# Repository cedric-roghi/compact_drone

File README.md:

# compact_drone
compact contra rotating drone

Progress Update (15/10/26):
- Tolerances have been tightened. Best method so far is to print everything very tight and to sand down parts with 1000 grit.
- Used Mistral AI to review my code and suggest adding a phase offset to the rotor controls. I had been focusing too much on drone control systems that I had overlooked critical physical effects of helicopter mechanical control systems. A phase offset of -25 degrees seems to remove most toilet bowl effect I was seeing.

https://github.com/user-attachments/assets/04978339-0f8a-490a-9869-5cce7a8ede1a

Progress Update (17/09/26):
- I have been making further tuning and tweaking to the PID gains.
- Built a simple landing gear system out of wood and a 3D printed adapter to screw onto the drone frame.
- I have got some first flight attempts with the drone hopping around the garden in a semi-controlled way.

https://github.com/user-attachments/assets/63424fa8-df9c-4474-a59d-4073fd4611da

Progress Update (09/09/26):
- The yaw controls are working. I have found some PID gains that seem stable at low and high rotor speeds. I am planning on making a PyQT application to adjust flight controller settings without flashing the microcontroller.
- I used hot glue to fix the servo motors more securely and printed some new link rods to reduce play in the swash-plate.
- The swash-plate currently has too much play where the drone cannot correct error when its too small and leads to uncontrollable oscillation.

https://github.com/user-attachments/assets/415317f5-2f4a-4eaa-9d52-048ebe863607

## Table of Contents
- [Requirements](#requirements)
- [Rationale](#rationale)
- [Installation](#installation)
- [Usage](#usage)
- [Features](#features)
- [Future_Additions](#future_additions)
- [Configuration](#configuration)
- [Known_Issues](#known_issues)

## Requirements
- Software:
    - Freecad (for 3D part design)
    - KICAD (PCB design)
    - ST Cube IDE (ST account required for download)
- Hardware:
    - BOM to come
    - Access to a 3D printer

## Rationale
I did not come up with the design idea of a tube shaped coaxial drone. Despite it being a rare design I got inspiration from projects such as [backcountrydrones](https://www.youtube.com/watch?v=82phDhYGT_0) and [Tdrone](https://github.com/ShenZhenAccelerationTechCo/Tdrone). BackcountryDrones guys have now changed to Ascent Aerosystems and make military/law enforcement and industrial coaxial drones. The NASA mars copter is another example of a contra rotating drone design.

The idea is that the propellers can fold down which means the drone can fit in smaller storage solutions. Not only does the the tube shape enable a smaller size when storing the drone but it also helps make it more rugged and resistant to poor treatment. A final goal for this project would be to have a drone I can strap to the outside of a hiking pack without having to worry about damage. 

Using a coaxial design is more efficient in theory. Having two large propeller spinning about the center of the drone increases the lifting disc area compared to having four propellers next to each other that will waste space. A coaxial drone with a tube shape also reduces its surface area when tilting forwards to move making it more streamlined than a quadcopter that shows more surface area to drag when moving forward. I recommend reading this paper from Ascent Aerosystems about all the advantages and its got diagrams (https://ascentaerosystems.com/wp-content/uploads/2024/12/Coaxial-Advantage-White-Paper-Ascent-AeroSystems.pdf).

Just because two propellers are stacked on top of each other does not actually mean I get double the lift of normal helicopter. Based on a small amount of research I have done, it would seem that while coaxial drones can be more efficient and reduce turbulent airflow they do not multiply thrust by two. Basically the thrust gain is not linear. Source (https://www.ligpower.com/blog/conventional-vs-coaxial-drone-motors.html).

Figures from the Ascent Aerosystems paper (https://ascentaerosystems.com/wp-content/uploads/2024/12/Coaxial-Advantage-White-Paper-Ascent-AeroSystems.pdf).

Some applications for the drone would be for survey work in remote areas, filming, compact and rapid deployment via stackable launch cells. In theory it could even be launched from a plane like the Atlantique 2 which already has tube shaped launchers on the belly for sonars. The mass plane launch system could enable for massive detailed search areas using drone swarms for any use case that would require a search area like pest control, mountain rescue, security perimeters.

Atlantique 2 sonar buoys launcher.

- STM32f411:
    - Same MCU I used for my turret project. Its fast, powerful, and has many timers for pwm output. Since I used it for a previous turret project it makes the PCB development for the drone much faster.
    - Another great advantage of this MCU is that it can do up to 100MHz clock speed which gives me plenty of headroom for "high speed"(relative term) communications like UART or I2C, without preempting my critical FreeRTOS tasks.

Below are some pictures of the PCB and 3D design to be printed.

## Installation
program command for usb in BOOT 0 mode

dfu-util -a 0 -s 0x08000000:leave -D build/debug/Drone_Code.bin

or use an stlinkv2.

## Usage

## Features
- Flight Controller
    -  ICM42605 IMU
    -  MMC5603NJ Magnetometer
    -  BMP280 Barometer
    -  2 USART connections for ELRS receiver and a future upgrade
    -  SWD connector for debugging/flashing
    -  Green and Red status LEDs
    -  BOOT0 switch (to switch bootloader mode)
    -  Reset button
    -  Extra servo PWM connector for camera pitch control (idea is that there is no need for yaw since the drone spins around easily)
 
- Mechanical
    - Foldable propellers
    - Fully 3D printed body
    - 
## Future_Additions

## Configuration

## Known_Issues

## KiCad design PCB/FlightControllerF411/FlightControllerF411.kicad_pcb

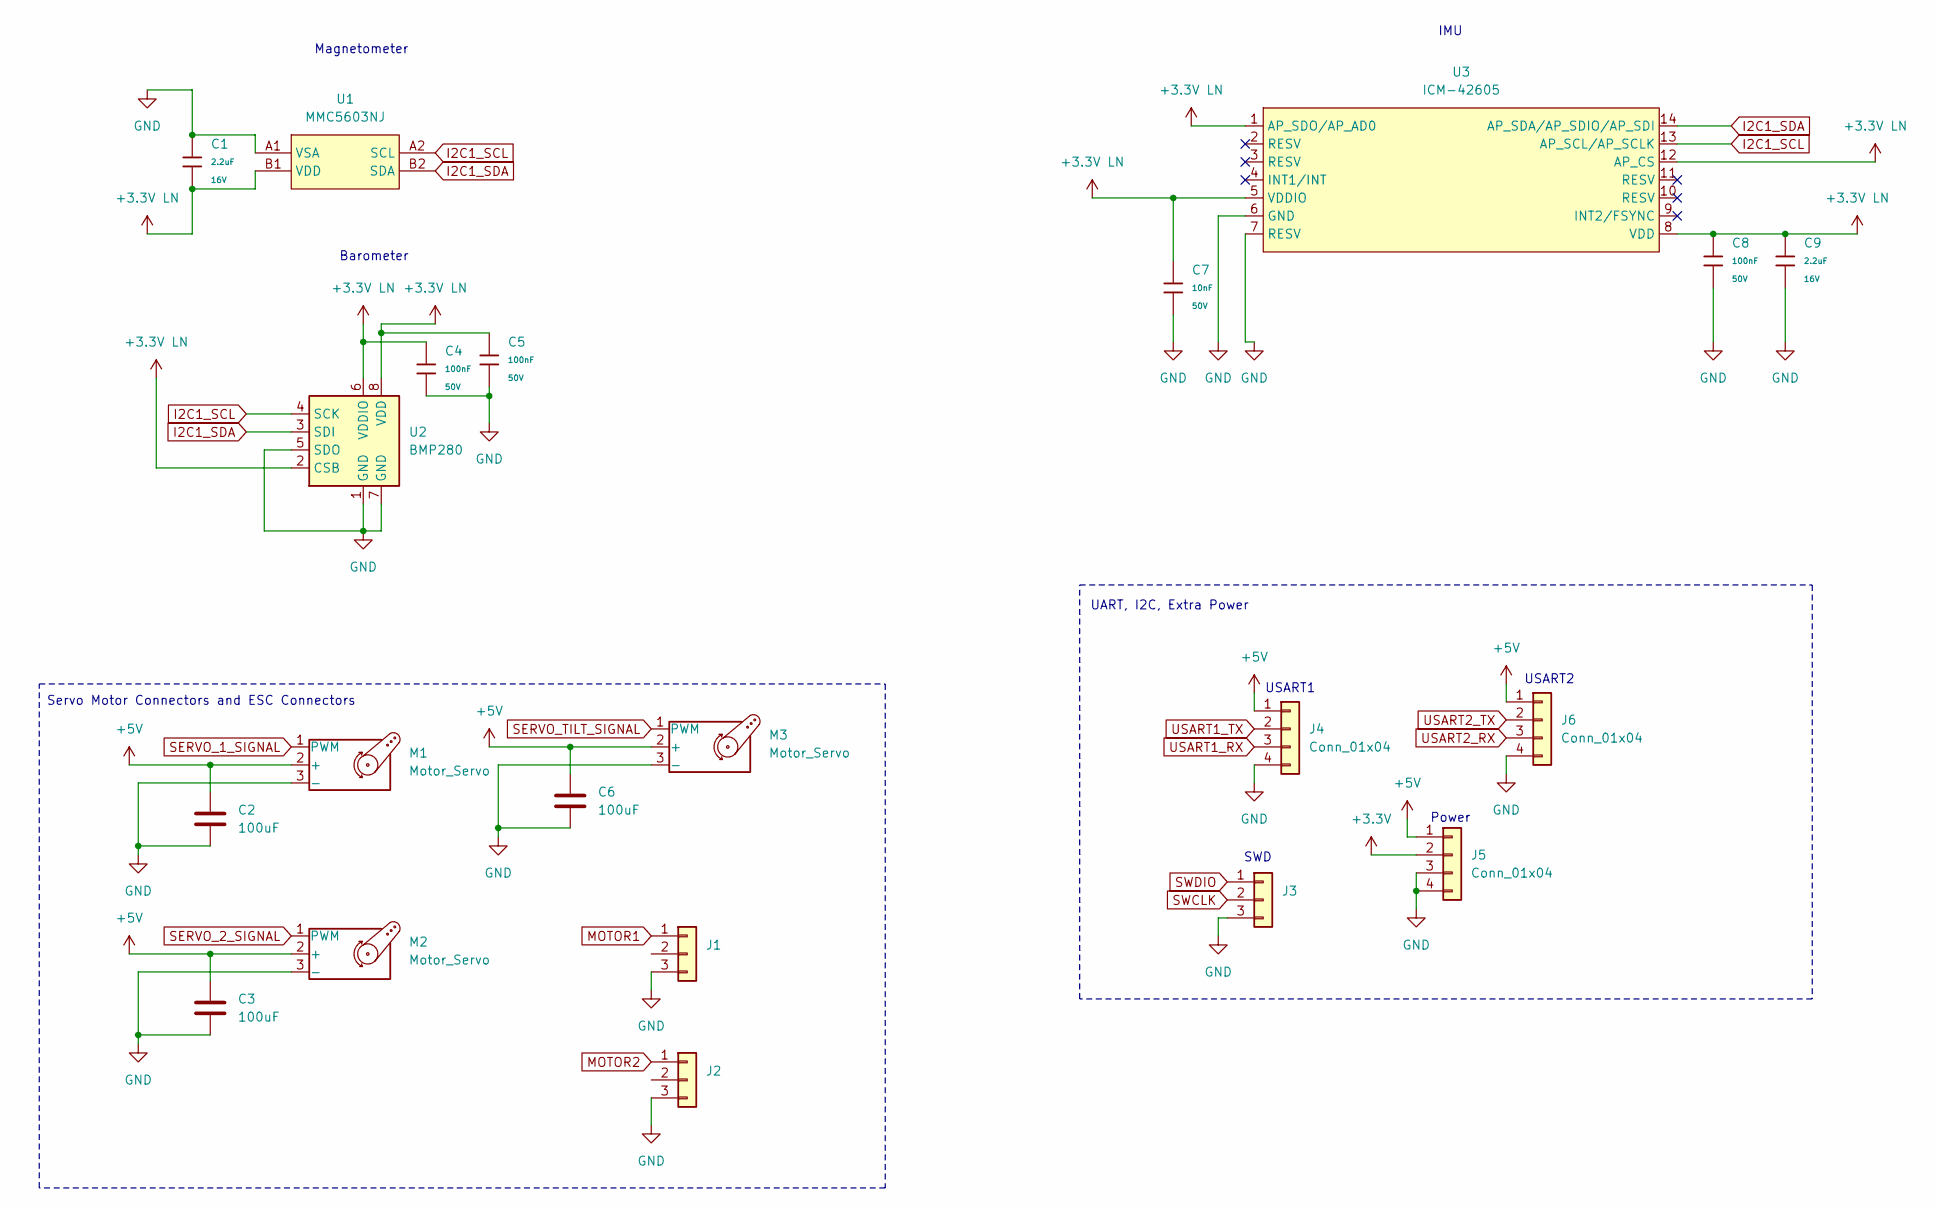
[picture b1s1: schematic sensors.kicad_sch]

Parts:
C1, C9: 2.2uF; C_0603; Voltage Rated 16V; Tolerance ±10%; Part CL10A225KO8NNNC; LCSC C23630
C2, C3, C6: 100uF; C_Radial_D6.3mm_H5.0mm_P2.50mm
C4, C5, C8: 100nF; C_0603; Voltage Rated 50V; Tolerance ±10%; Part CC0603KRX7R9BB104; LCSC C14663
C7: 10nF; C_0603; Voltage Rated 50V; Tolerance ±10%; Part 0603B103K500NT; LCSC C57112
J1, J2, J3: Conn_01x03; PinHeader_1x03_P2.54mm_Vertical
J4, J5, J6: Conn_01x04; PinHeader_1x04_P2.54mm_Vertical
M1, M2, M3: Motor_Servo; PinHeader_1x03_P2.54mm_Vertical
U1: MMC5603NJ; FLIPCHIP-4_L0.8-W0.8-R2-C2-P0.40-TL; MPN MMC5603NJ; LCSC Part C404328
U2: BMP280; Bosch_LGA-8_2x2.5mm_P0.65mm_ClockwisePinNumbering
U3: ICM-42605; LGA-14_L3.0-W2.5-P0.50-TL; MPN ICM-42605; LCSC Part C2655099

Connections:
+3.3V: J5.2; also elsewhere on the board
+3.3V LN: C1.2, C4.1, C5.1, C7.1, C8.1, C9.1, U1.B1 (VDD), U2.2 (CSB), U2.6 (VDDIO), U2.8 (VDD), U3.1 (AP_SDO/AP_AD0), U3.5 (VDDIO), U3.8 (VDD), U3.12 (AP_CS); also elsewhere on the board
+5V: C2.1, C3.1, C6.1, J4.1, J5.1, J6.1, M1.2 (+), M2.2 (+), M3.2 (+); also elsewhere on the board
GND: C1.1, C2.2, C3.2, C4.2, C5.2, C6.2, C7.2, C8.2, C9.2, J1.3, J2.3, J3.3, J4.4, J5.3, J5.4, J6.4, M1.3 (-), M2.3 (-), M3.3 (-), U1.A1 (VSA), U2.1 (GND), U2.5 (SDO), U2.7 (GND), U3.6 (GND), U3.7 (RESV); also elsewhere on the board
I2C1_SCL: U1.A2 (SCL), U2.4 (SCK), U3.13 (AP_SCL/AP_SCLK); also elsewhere on the board
I2C1_SDA: U1.B2 (SDA), U2.3 (SDI), U3.14 (AP_SDA/AP_SDIO/AP_SDI); also elsewhere on the board
MOTOR1: J1.1; also elsewhere on the board
MOTOR2: J2.1; also elsewhere on the board
SERVO_1_SIGNAL: M1.1 (PWM); also elsewhere on the board
SERVO_2_SIGNAL: M2.1 (PWM); also elsewhere on the board
SERVO_TILT_SIGNAL: M3.1 (PWM); also elsewhere on the board
SWCLK: J3.2; also elsewhere on the board
SWDIO: J3.1; also elsewhere on the board
USART1_RX: J4.3; also elsewhere on the board
USART1_TX: J4.2; also elsewhere on the board
USART2_RX: J6.3; also elsewhere on the board
USART2_TX: J6.2; also elsewhere on the board

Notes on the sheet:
USART1
Servo Motor Connectors and ESC Connectors
UART, I2C, Extra Power
Power
SWD
Magnetometer
Barometer
IMU
USART2

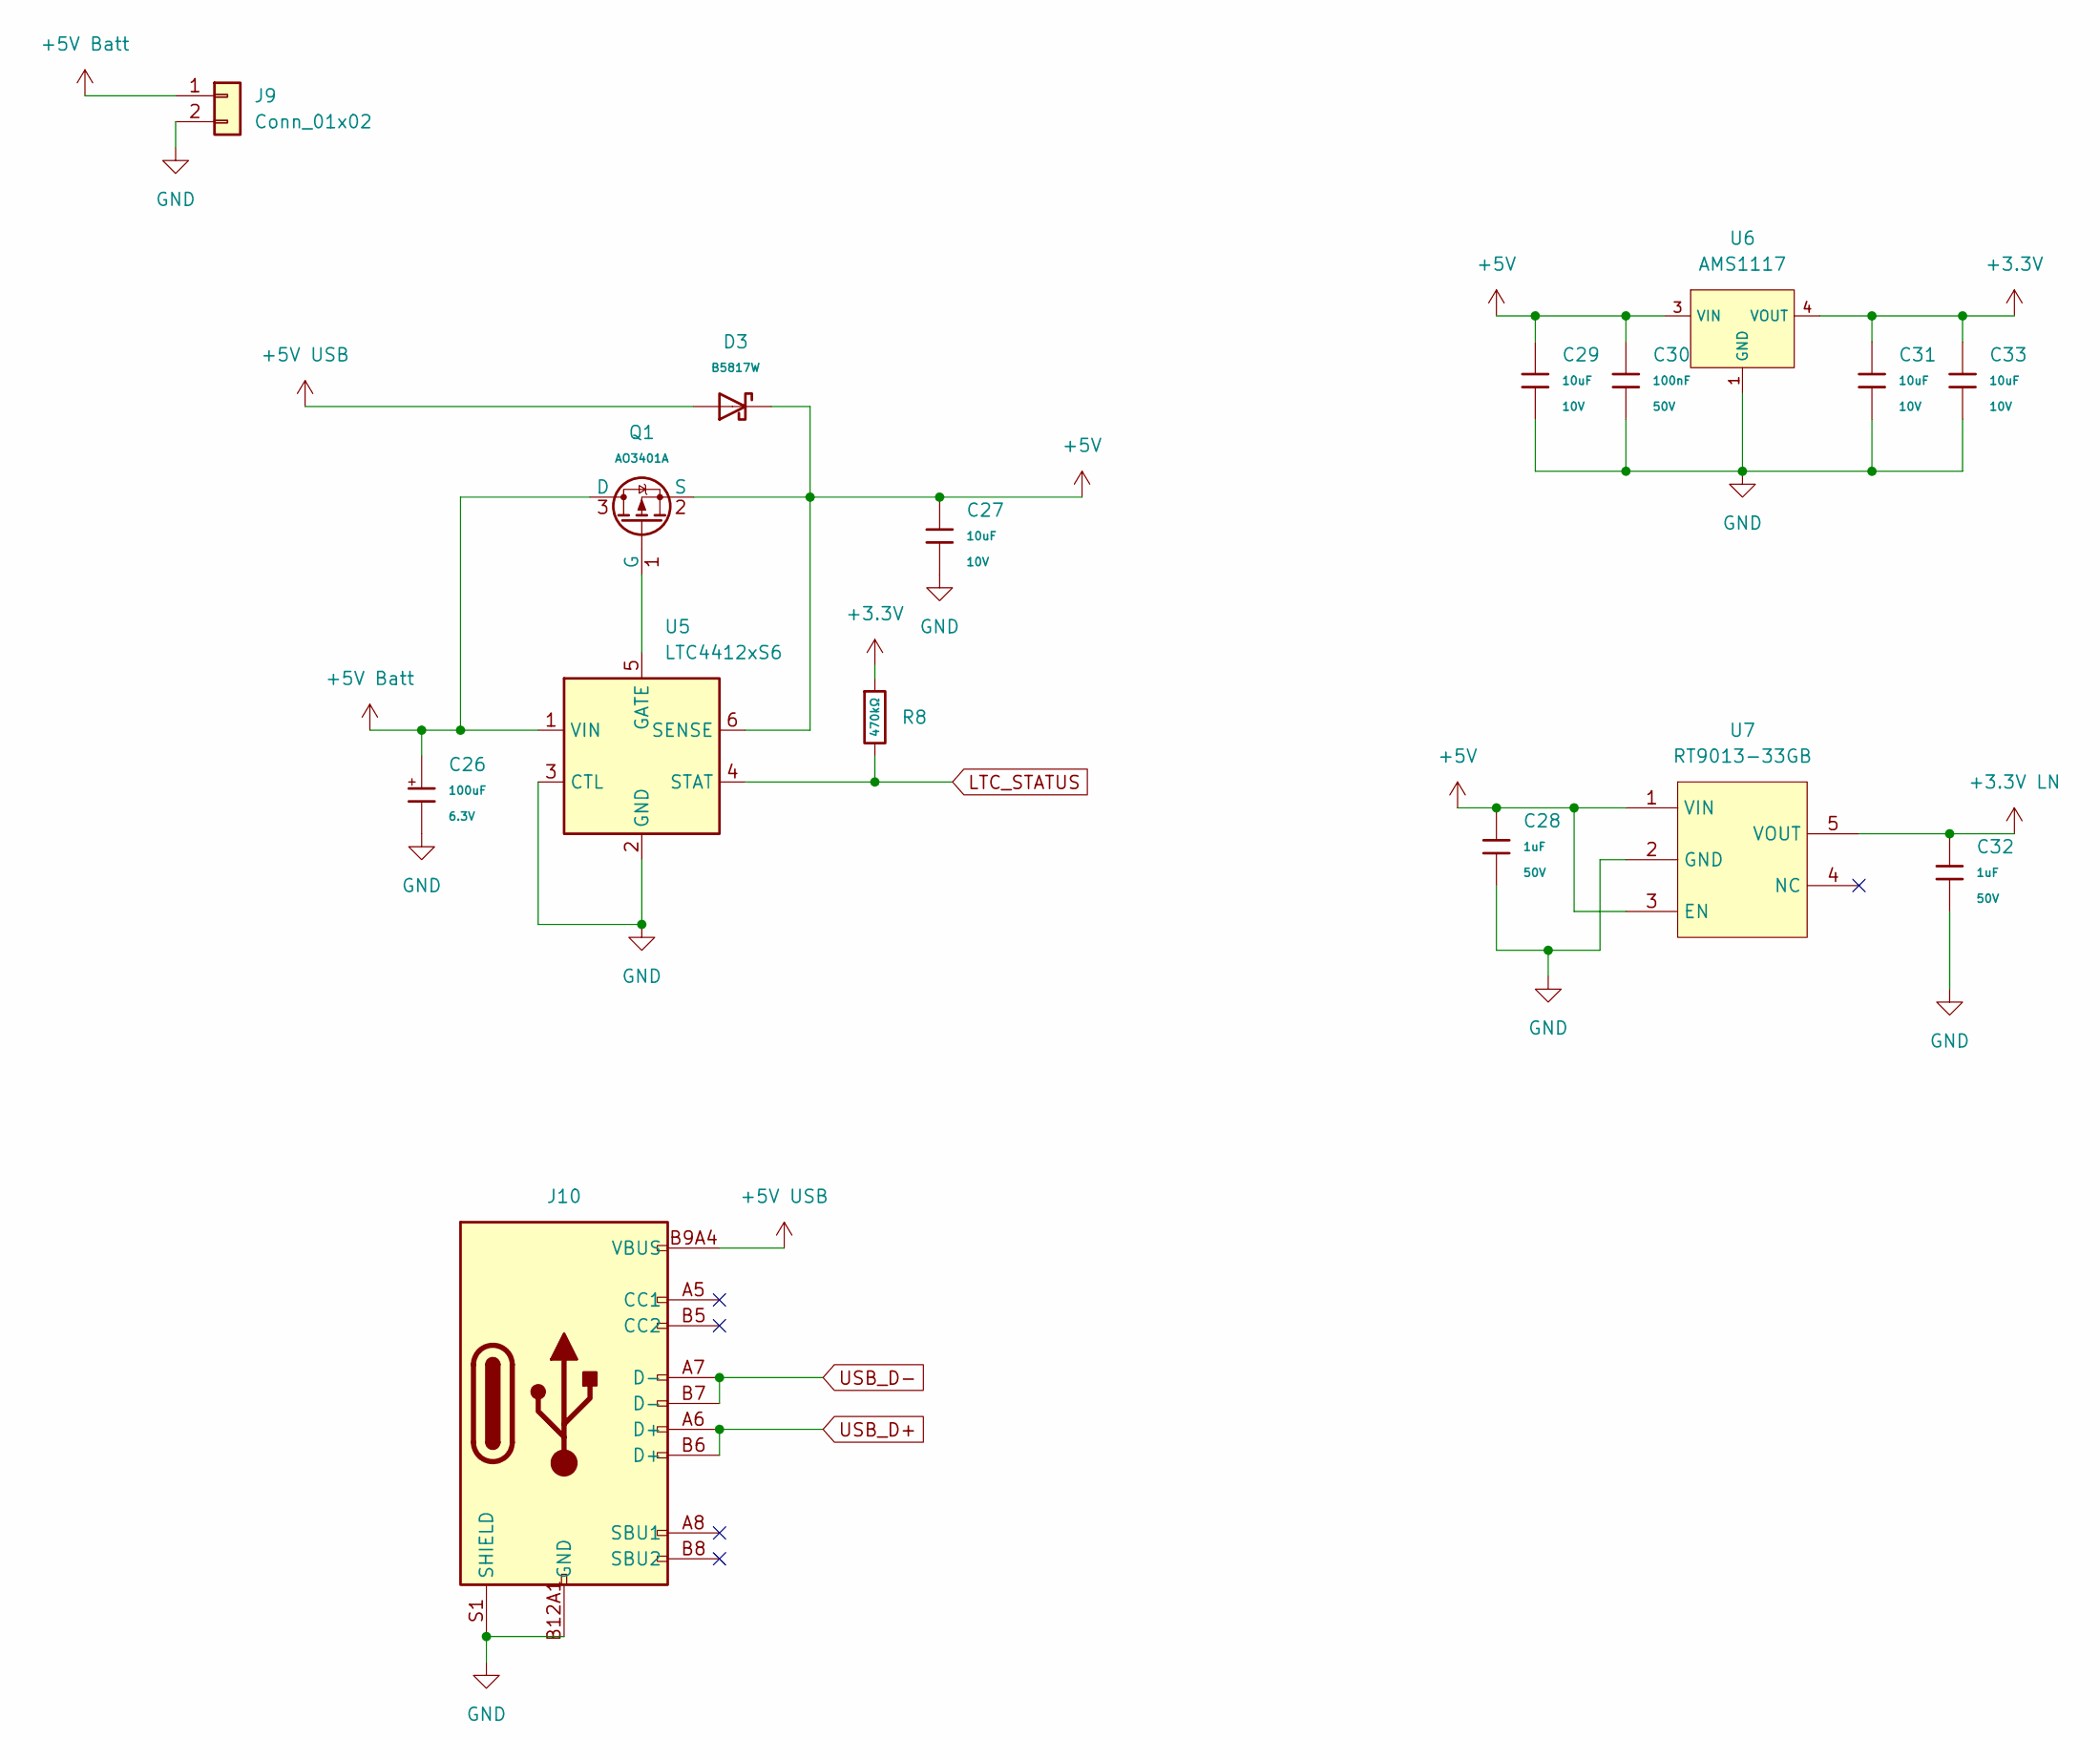
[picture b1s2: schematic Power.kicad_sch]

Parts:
C26: 100uF; C_CASE-B-3528-21(mm); Tolerance ±10%; Rated Voltage 6.3V; Part TAJB107K006RNJ; LCSC C16133
C27, C29, C31, C33: 10uF; C_0603; Voltage Rated 10V; Tolerance ±10%; Part CL10A106KP8NNNC; LCSC C19702
C28, C32: 1uF; C_0603; Voltage Rated 50V; Tolerance ±10%; Part CL10A105KB8NNNC; LCSC C15849
C30: 100nF; C_0603; Voltage Rated 50V; Tolerance ±10%; Part CC0603KRX7R9BB104; LCSC C14663
D3: B5817W; D_SOD-123; Forward Voltage (Vf@If) 0.45V@1.0A; Reverse Voltage (Vr) 20V; Part B5817W; LCSC C7420328
J9: Conn_01x02; PinHeader_1x02_P2.54mm_Vertical
J10: Connector, USB-TYPE-C-16P; TYPE-C-SMD_HX-TYPE-C-16PIN; LCSC C2927039
Q1: AO3401A; Q_SOT-23; Part AO3401A; LCSC C15127
R8: 470kΩ; R_0603; Overload Voltage (Max) 75V; Tolerance ±1%; Part 0603WAF4703T5E; LCSC C23178
U5: LTC4412xS6; TSOT-23-6
U6: AMS1117; SOT-223-3_L6.5-W3.4-P2.30-LS7.0-BR; Output Voltage 3.3V; Dropout Voltage 1.3V@(800mA); Part AMS1117-3.3; LCSC C6186
U7: RT9013-33GB; SOT-23-5_L3.0-W1.7-P0.95-LS2.8-BL; MPN RT9013-33GB; LCSC Part C47773

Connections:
+3.3V: C31.1, C33.1, R8.1, U6.2 (VOUT), U6.4 (VOUT); also elsewhere on the board
+3.3V LN: C32.1, U7.5 (VOUT); also elsewhere on the board
+5V: C27.1, C28.1, C29.1, C30.1, D3.1, Q1.2 (S), U5.6 (SENSE), U6.3 (VIN), U7.1 (VIN), U7.3 (EN); also elsewhere on the board
+5V Batt: C26.1, J9.1, Q1.3 (D), U5.1 (VIN)
+5V USB: D3.2, J10.A9B4 (VBUS), J10.B9A4 (VBUS)
GND: C26.2, C27.2, C28.2, C29.2, C30.2, C31.2, C32.2, C33.2, J9.2, J10.A12B1 (GND), J10.B12A1 (GND), J10.S1 (SHIELD), U5.2 (GND), U5.3 (CTL), U6.1 (GND), U7.2 (GND); also elsewhere on the board
LTC_STATUS: R8.2, U5.4 (STAT)
unnamed: Q1.1 (G), U5.5 (GATE)
USB_D+: J10.A6 (D+), J10.B6 (D+); also elsewhere on the board
USB_D-: J10.A7 (D-), J10.B7 (D-); also elsewhere on the board

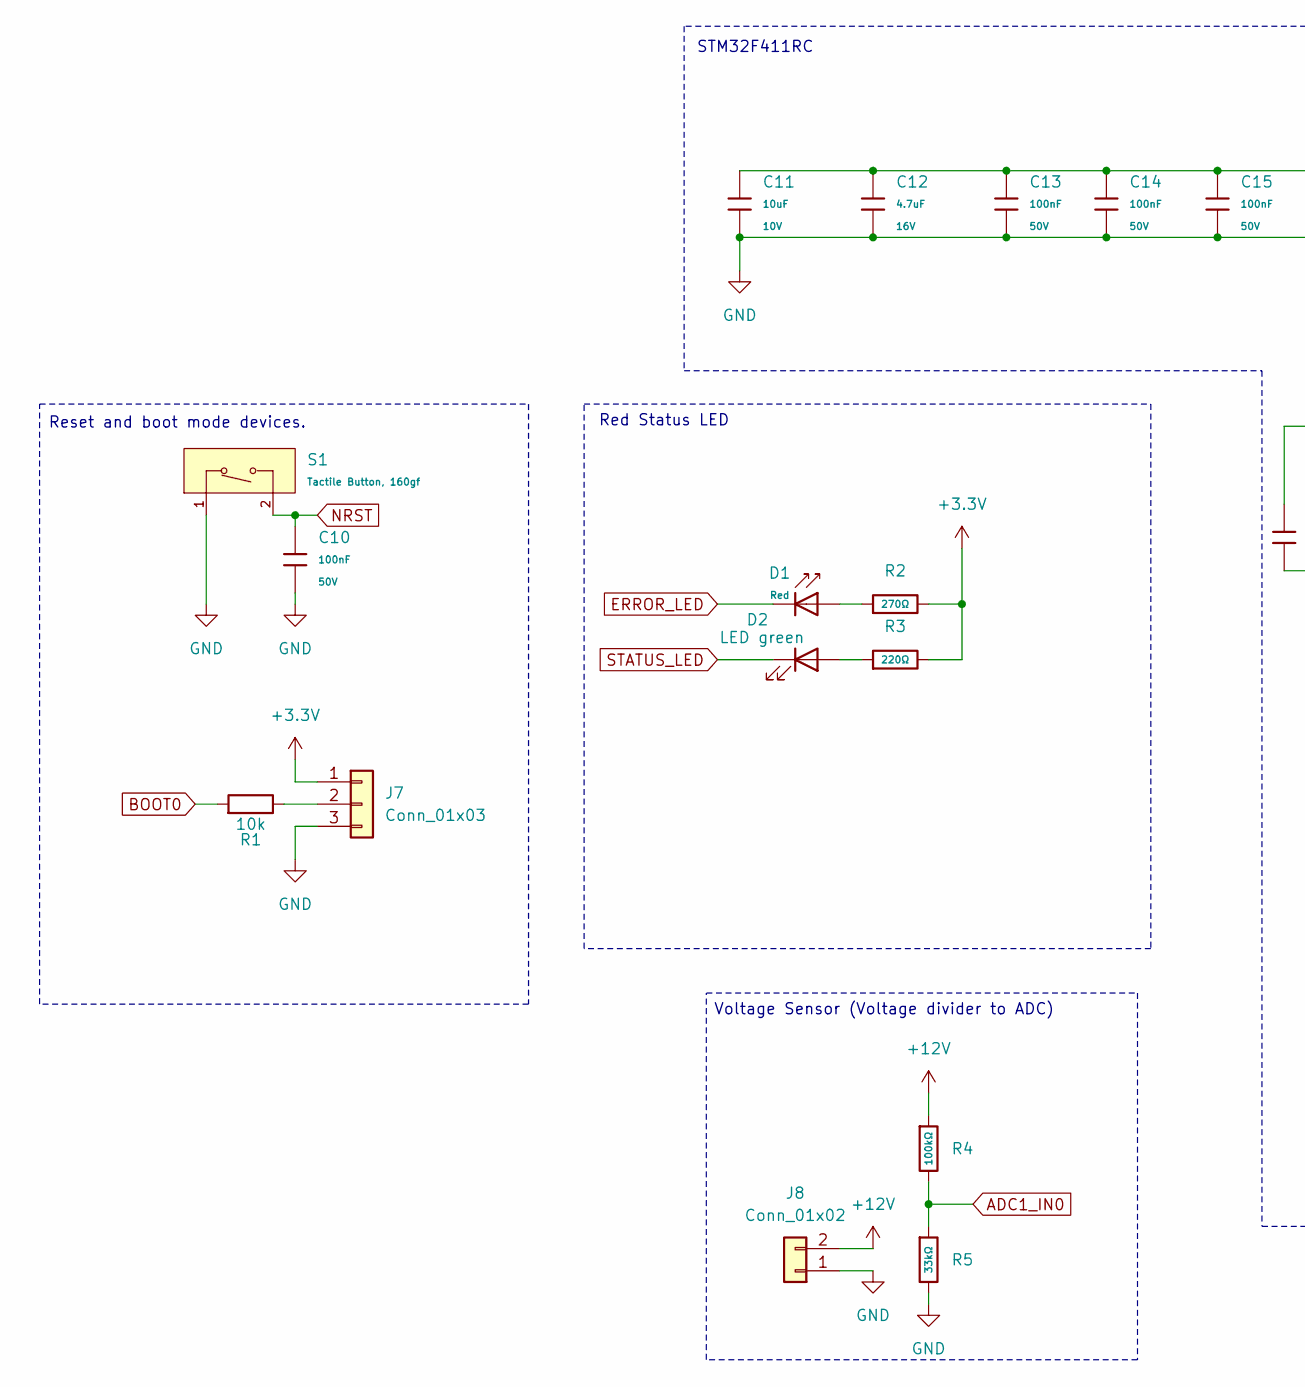
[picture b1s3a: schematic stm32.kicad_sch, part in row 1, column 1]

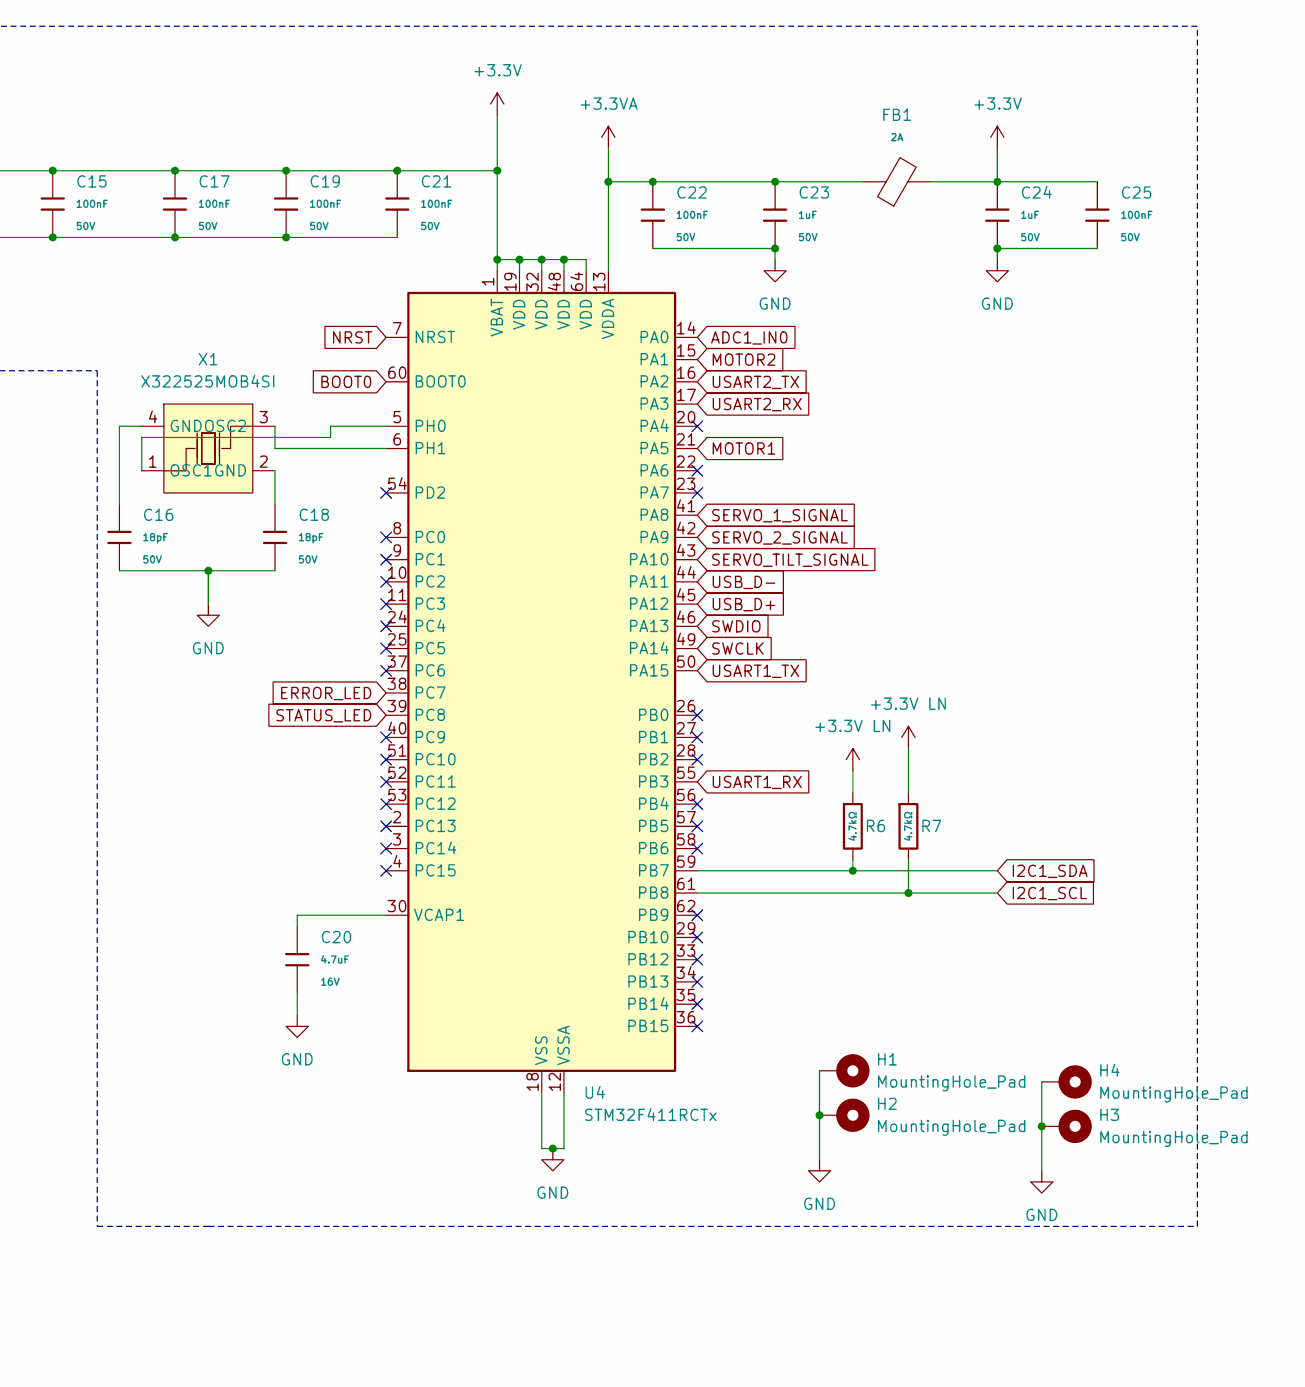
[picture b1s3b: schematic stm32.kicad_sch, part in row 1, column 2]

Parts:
C10, C13, C14, C15, C17, C19, C21, C22, C25: 100nF; C_0603; Voltage Rated 50V; Tolerance ±10%; Part CC0603KRX7R9BB104; LCSC C14663
C11: 10uF; C_0603; Voltage Rated 10V; Tolerance ±10%; Part CL10A106KP8NNNC; LCSC C19702
C12, C20: 4.7uF; C_0603; Voltage Rated 16V; Tolerance ±10%; Part CL10A475KO8NNNC; LCSC C19666
C16, C18: 18pF; C_0603; Voltage Rated 50V; Tolerance ±5%; Part CL10C180JB8NNNC; LCSC C1647
C23, C24: 1uF; C_0603; Voltage Rated 50V; Tolerance ±10%; Part CL10A105KB8NNNC; LCSC C15849
D1: Red; D_0603; Part KT-0603R; LCSC C2286
D2: LED green; LED_0603_1608Metric_Pad1.05x0.95mm_HandSolder
FB1: FB_0603; Current Rating 2A; Tolerance ±25%; Part BLM18PG121SN1D; LCSC C14709
H1, H2, H3, H4: MountingHole_Pad; MountingHole_2.7mm_M2.5_DIN965_Pad
J7: Conn_01x03; PinHeader_1x03_P2.54mm_Vertical
J8: Conn_01x02; PinHeader_1x02_P2.54mm_Vertical
R1: 10k; R_0603_1608Metric_Pad0.98x0.95mm_HandSolder
R2: 270Ω; R_0603; Overload Voltage (Max) 75V; Tolerance ±1%; Part 0603WAF2700T5E; LCSC C22966
R3: 220Ω; R_0603; Overload Voltage (Max) 75V; Tolerance ±1%; Part 0603WAF2200T5E; LCSC C22962
R4: 100kΩ; R_0603; Overload Voltage (Max) 75V; Tolerance ±1%; Part 0603WAF1003T5E; LCSC C25803
R5: 33kΩ; R_0603; Overload Voltage (Max) 75V; Tolerance ±1%; Part 0603WAF3302T5E; LCSC C4216
R6, R7: 4.7kΩ; R_0603; Overload Voltage (Max) 75V; Tolerance ±1%; Part 0603WAF4701T5E; LCSC C23162
S1: Tactile Button, 160gf; SW_TS-1088-AR02016; Voltage Rating (Dc) 12V; Part TS-1088-AR02016; LCSC C720477
U4: STM32F411RCTx; LQFP-64_10x10mm_P0.5mm
X1: X322525MOB4SI; CRYSTAL-SMD_4P-L3.2-W2.5-BL; MPN X322525MOB4SI; LCSC Part C9006

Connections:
+3.3V: C11.1, C12.1, C13.1, C14.1, C15.1, C17.1, C19.1, C21.1, C24.1, C25.1, FB1.2, J7.1, R2.2, R3.2, U4.1 (VBAT), U4.19 (VDD), U4.32 (VDD), U4.48 (VDD), U4.64 (VDD); also elsewhere on the board
+3.3V LN: R6.1, R7.1; also elsewhere on the board
+3.3VA: C22.1, C23.1, FB1.1, U4.13 (VDDA)
+12V: J8.2, R4.1
ADC1_IN0: R4.2, R5.1, U4.14 (PA0)
BOOT0: R1.2, U4.60 (BOOT0)
ERROR_LED: D1.1, U4.38 (PC7)
GND: C10.2, C11.2, C12.2, C13.2, C14.2, C15.2, C16.2, C17.2, C18.2, C19.2, C20.2, C21.2, C22.2, C23.2, C24.2, C25.2, H1.1 (1_1), H2.1 (1_1), H3.1 (1_1), H4.1 (1_1), J7.3, J8.1, R5.2, S1.1 (A), U4.12 (VSSA), U4.18 (VSS), U4.31 (VSS), U4.47 (VSS), U4.63 (VSS); also elsewhere on the board
I2C1_SCL: R7.2, U4.61 (PB8); also elsewhere on the board
I2C1_SDA: R6.2, U4.59 (PB7); also elsewhere on the board
MOTOR1: U4.21 (PA5); also elsewhere on the board
MOTOR2: U4.15 (PA1); also elsewhere on the board
NRST: C10.1, S1.2 (B), U4.7 (NRST)
unnamed: C16.1, X1.4 (GND)
unnamed: C18.1, X1.2 (GND)
unnamed: D1.2, R2.1
unnamed: D2.2 (A), R3.1
unnamed: J7.2, R1.1
unnamed: U4.5 (PH0), X1.1 (OSC1)
unnamed: U4.6 (PH1), X1.3 (OSC2)
unnamed: C20.1, U4.30 (VCAP1)
SERVO_1_SIGNAL: U4.41 (PA8); also elsewhere on the board
SERVO_2_SIGNAL: U4.42 (PA9); also elsewhere on the board
SERVO_TILT_SIGNAL: U4.43 (PA10); also elsewhere on the board
STATUS_LED: D2.1 (K), U4.39 (PC8)
SWCLK: U4.49 (PA14); also elsewhere on the board
SWDIO: U4.46 (PA13); also elsewhere on the board
USART1_RX: U4.55 (PB3); also elsewhere on the board
USART1_TX: U4.50 (PA15); also elsewhere on the board
USART2_RX: U4.17 (PA3); also elsewhere on the board
USART2_TX: U4.16 (PA2); also elsewhere on the board
USB_D+: U4.45 (PA12); also elsewhere on the board
USB_D-: U4.44 (PA11); also elsewhere on the board

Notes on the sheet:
Red Status LED
STM32F411RC
Voltage Sensor (Voltage divider to ADC)
Reset and boot mode devices.

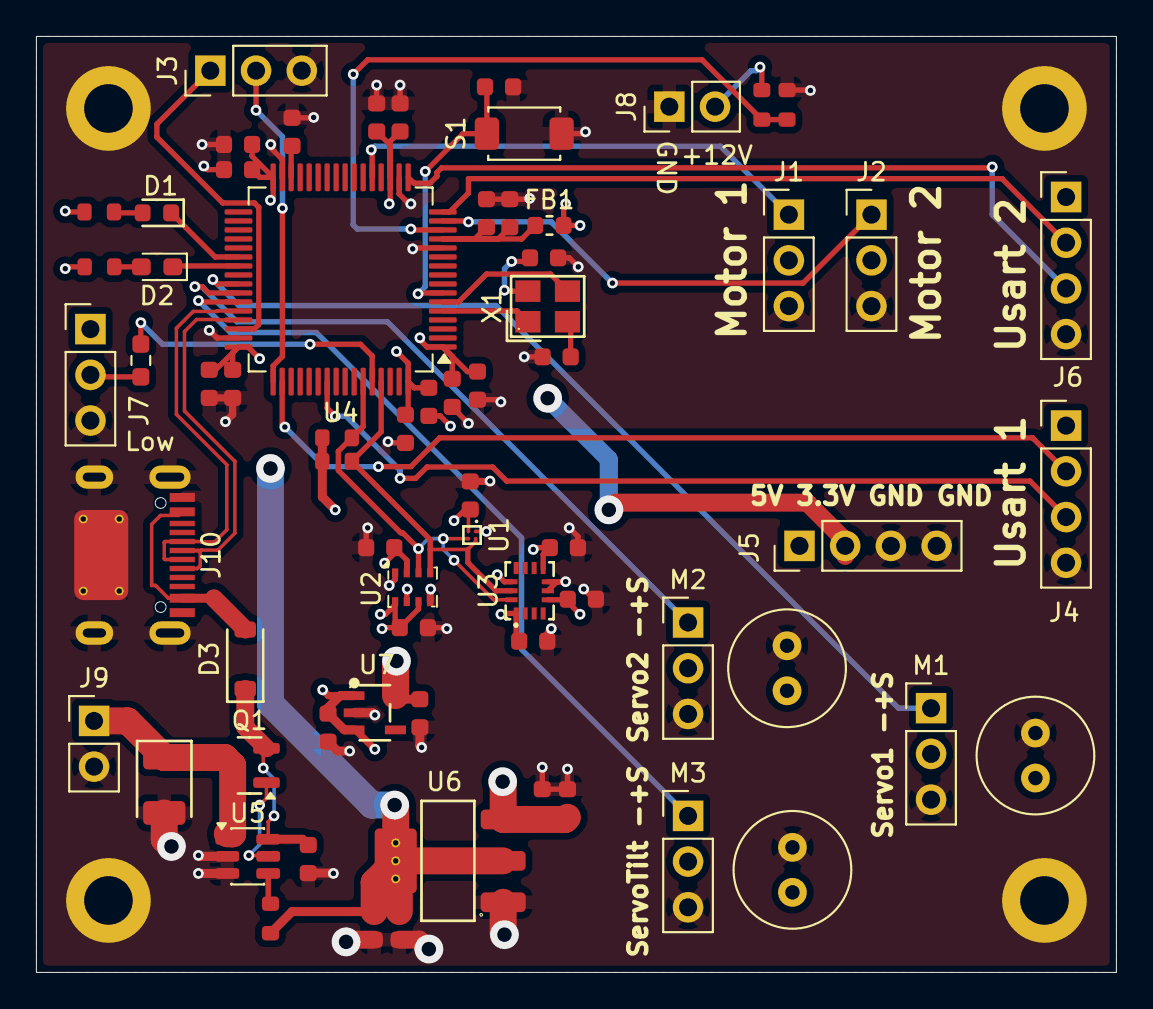
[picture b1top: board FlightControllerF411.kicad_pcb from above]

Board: 4 copper layers, 60.0 x 52.0 mm, 72 parts (0 on the bottom side), 38 nets.

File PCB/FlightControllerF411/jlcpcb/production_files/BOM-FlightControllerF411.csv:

Comment,Designator,Footprint,LCSC,Quantity
100kΩ,R4,R_0603,C25803,1
100nF,"C10,C13,C14,C15,C17,C19,C21,C22,C25,C30,C4,C5,C8",C_0603,C14663,13
100uF,C26,C_CASE-B-3528-21(mm),C16133,1
10k,R1,R_0603_1608Metric_Pad0.98x0.95mm_HandSolder,C25805,1
10nF,C7,C_0603,C57112,1
10uF,"C11,C27,C29,C31,C33",C_0603,C19702,5
18pF,"C16,C18",C_0603,C1647,2
1uF,"C23,C24,C28,C32",C_0603,C15849,4
2.2uF,"C1,C9",C_0603,C23630,2
220Ω,R3,R_0603,C22962,1
270Ω,R2,R_0603,C22966,1
33kΩ,R5,R_0603,C4216,1
4.7kΩ,"R6,R7",R_0603,C23162,2
4.7uF,"C12,C20",C_0603,C19666,2
470kΩ,R8,R_0603,C23178,1
AMS1117,U6,SOT-223-3_L6.5-W3.4-P2.30-LS7.0-BR,C6186,1
AO3401A,Q1,Q_SOT-23,C15127,1
B5817W,D3,D_SOD-123,C7420328,1
BMP280,U2,Bosch_LGA-8_2x2.5mm_P0.65mm_ClockwisePinNumbering,C83291,1
"Connector, USB-TYPE-C-16P",J10,TYPE-C-SMD_HX-TYPE-C-16PIN,C2927039,1
ICM-42605,U3,LGA-14_L3.0-W2.5-P0.50-TL,C2655099,1
LTC4412xS6,U5,TSOT-23-6,C514442,1
MMC5603NJ,U1,FLIPCHIP-4_L0.8-W0.8-R2-C2-P0.40-TL,C404328,1
RT9013-33GB,U7,SOT-23-5_L3.0-W1.7-P0.95-LS2.8-BL,C47773,1
STM32F411RCTx,U4,LQFP-64_10x10mm_P0.5mm,C222222,1
"Tactile Button, 160gf",S1,SW_TS-1088-AR02016,C720477,1
X322525MOB4SI,X1,CRYSTAL-SMD_4P-L3.2-W2.5-BL,C9006,1
~,FB1,FB_0603,C14709,1

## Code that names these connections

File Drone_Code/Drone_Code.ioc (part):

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Mcu.Name=STM32F411R(C-E)Tx
Mcu.Package=LQFP64
Mcu.UserName=STM32F411RCTx
PA0-WKUP.Signal=ADCx_IN0
PA1.GPIOParameters=GPIO_Label
PA1.GPIO_Label=Motor 2
PA1.Signal=S_TIM2_CH2
PA10.GPIOParameters=GPIO_Label
PA10.GPIO_Label=Servo Tilt
PA10.Signal=S_TIM1_CH3
PA11.Mode=Device_Only
PA11.Signal=USB_OTG_FS_DM
PA12.Mode=Device_Only
PA12.Signal=USB_OTG_FS_DP
PA13.Mode=Serial_Wire
PA13.Signal=SYS_JTMS-SWDIO
PA14.Mode=Serial_Wire
PA14.Signal=SYS_JTCK-SWCLK
PA15.Mode=Asynchronous
PA15.Signal=USART1_TX
PA2.Mode=Asynchronous
PA2.Signal=USART2_TX
PA3.Mode=Asynchronous
PA3.Signal=USART2_RX
PA5.GPIOParameters=GPIO_Label
PA5.GPIO_Label=Motor 1
PA5.Signal=S_TIM2_CH1_ETR
PA8.GPIOParameters=GPIO_Label
PA8.GPIO_Label=Servo 1
PA8.Signal=S_TIM1_CH1
PA9.GPIOParameters=GPIO_Label
PA9.GPIO_Label=Servo 2
PA9.Signal=S_TIM1_CH2
PB3.Mode=Asynchronous
PB3.Signal=USART1_RX
PB7.Mode=I2C
PB7.Signal=I2C1_SDA
PB8.Mode=I2C
PB8.Signal=I2C1_SCL
PC7.Signal=GPIO_Output
PC8.Signal=GPIO_Output
PH0\ -\ OSC_IN.Mode=HSE-External-Oscillator
PH0\ -\ OSC_IN.Signal=RCC_OSC_IN
PH1\ -\ OSC_OUT.Mode=HSE-External-Oscillator
PH1\ -\ OSC_OUT.Signal=RCC_OSC_OUT
RCC.HSE_VALUE=25000000
RCC.SYSCLKFreq_VALUE=96000000
RCC.SYSCLKSource=RCC_SYSCLKSOURCE_PLLCLK
board=custom

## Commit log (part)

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2026-03-16 small commit to put things back to date
